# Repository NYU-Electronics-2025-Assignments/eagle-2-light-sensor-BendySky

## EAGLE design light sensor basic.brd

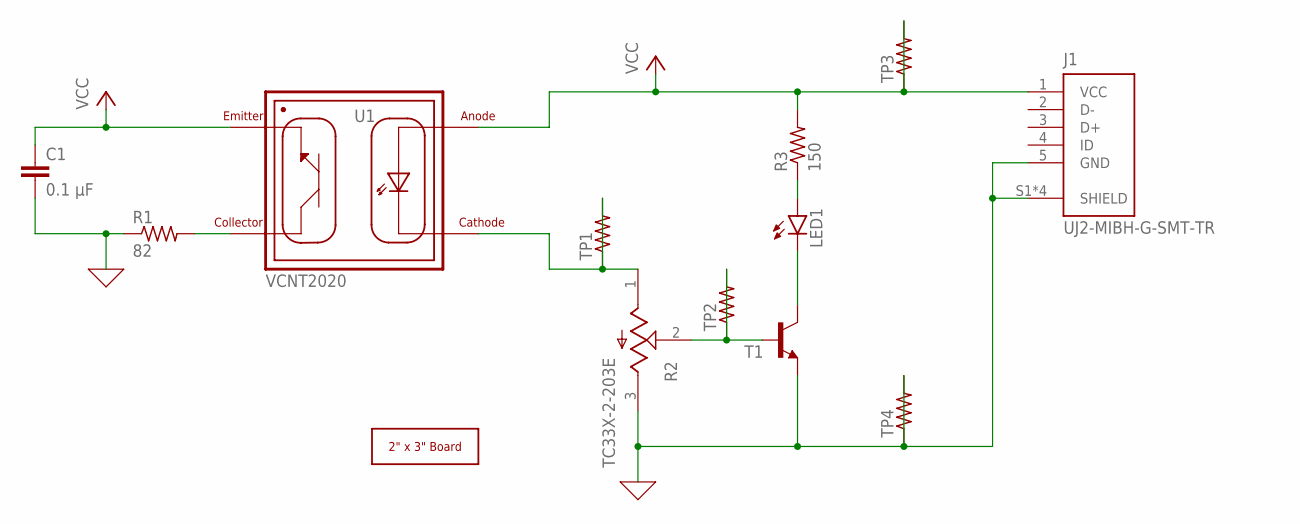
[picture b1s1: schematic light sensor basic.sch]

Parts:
C1: 0.1 µF; C1206
J1: UJ2-MIBH-G-SMT-TR; CUI_UJ2-MIBH-G-SMT-TR
LED1: LEDCHIPLED_0805; CHIPLED_0805
R1: 82; R0805
R2: TC33X-2-203E; TRIM_TC33X-2-203E
R3: 150; R0805
T1: BFS17-NPN-SOT23-BEC; SOT23-BEC
TP1, TP2, TP3, TP4: R-US_R1206; R1206
U1: VCNT2020; XDCR_VCNT2020
U$1: 2X3_BOARD_V2

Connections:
0: C1.2, J1.5 (GND), J1.S1 (SHIELD), J1.S2 (SHIELD), J1.S3 (SHIELD), J1.S4 (SHIELD), R1.1, R2.3 (CW), T1.E, TP4.1, TP4.2
unnamed: R2.2 (W), T1.B, TP2.1, TP2.2
unnamed: R1.2, U1.2 (COLLECTOR)
unnamed: LED1.C, T1.C
unnamed: R2.1 (CCW), TP1.1, TP1.2, U1.4 (CATHODE)
unnamed: LED1.A, R3.1
VCC: C1.1, J1.1 (VCC), R3.2, TP3.1, TP3.2, U1.1 (EMITTER), U1.3 (ANODE)

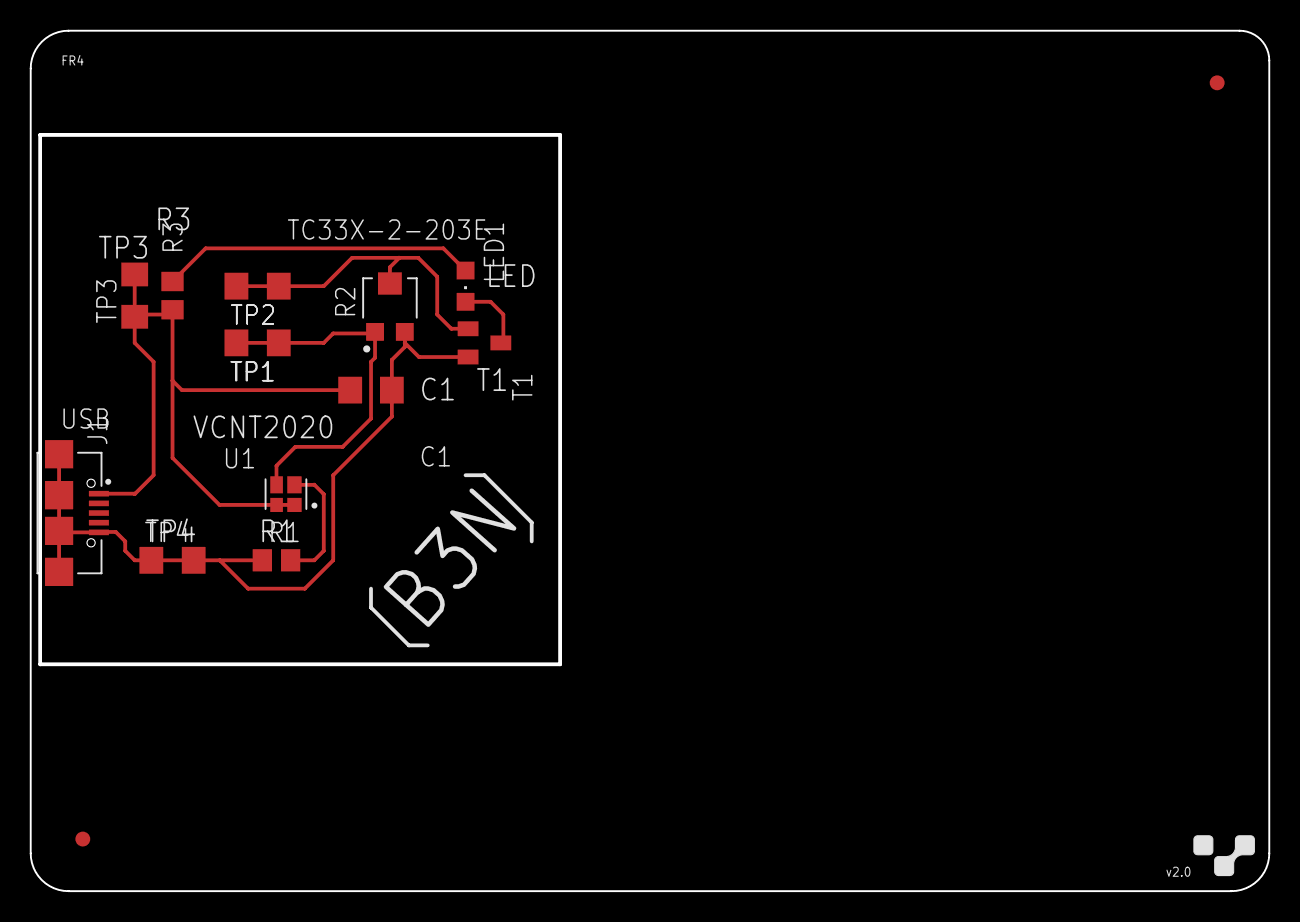
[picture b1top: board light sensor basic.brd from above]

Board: 2 copper layers, 83.1 x 57.7 mm, 13 parts (0 on the bottom side), 7 nets.

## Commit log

2025-02-25 schematic drawn
2025-02-28 gerber files
